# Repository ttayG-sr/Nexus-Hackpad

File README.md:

# Nexus-Hackpad
  Nexus Pad is a 9-key macro pad with a rotary encoder and an OLED, with the switches illuminated by LED backlighting! It is made for compact keyboard gaming, specifically Valorant, and, in the future, a Home Control Panel for smart devices; it functions using QMK firmware.

## Features:
- 9 MX-Style switches
  
- Rotary Encoder
  
- 0.91 inch, 128x32 OLED Screen
  
- 9 SK6812 Mini-E LEDs
  
- 70mm x 100mm Custom PCB
  
- 2 Part Custom Case
  
- All brought together with the Seeed XIAO RP2040 using QMK firmware
  
## CAD Model:
  It is made with a sandwich-style mount, using supports to elevate the PCB so the USB port can fit, and the switches and everything else have the necessary tolerance. 

  The PCB is sandwiched between the bottom case, which has the supports, and the top plate, all fastened with M3 Heat Inserts and screws.
Additionally, I rounded everything for moderate viewing angles for the OLED and a more aesthetic look.

<p align="center">Exploded View:</p>

## PCB:
This is the PCB that connects all of my components and houses the brain of the Nexus Pad; it was all made in KiCAD.

<p align="center">Schematic:</p>

<p align="center">PCB:</p>

## Firmware Overview:

The Nexus Pad uses QMK (https://qmk.fm/) to operate.

- Key Bindings
  - 4 for abilities in Valorant
  - A Left Shift to walk in Valorant
  - Another layer in the future will be added for productivity tools
  - Will include support for VIA in the future for more customizability!
- The rotary encoder can control the volume; the press function doesn't work.
- I plan for the OLED to show CPU and GPU temperatures in the future using plugins, but for now it just displays "Nexus Pad"
- The LEDs have three lighting effects: breathing, rainbow mood, and snake.

## BOM:
- 1x SEEED Xiao RP2040
- 9x 1N4148 DO-35 Diodes
- 9x MX-Style switches
- 9x DSA Keycaps
- 9x SK6812 MINI-E LEDs
- 1x EC11 Rotary Encoder
- 1x 0.91" 128x32 OLED Display
- 1x PCB
- 4x M3x16mm screws
- 4x M3x5mx4mm heatset inserts
- 1x Bottom case (3D Printed)
- 1x Top plate (3D Printed)

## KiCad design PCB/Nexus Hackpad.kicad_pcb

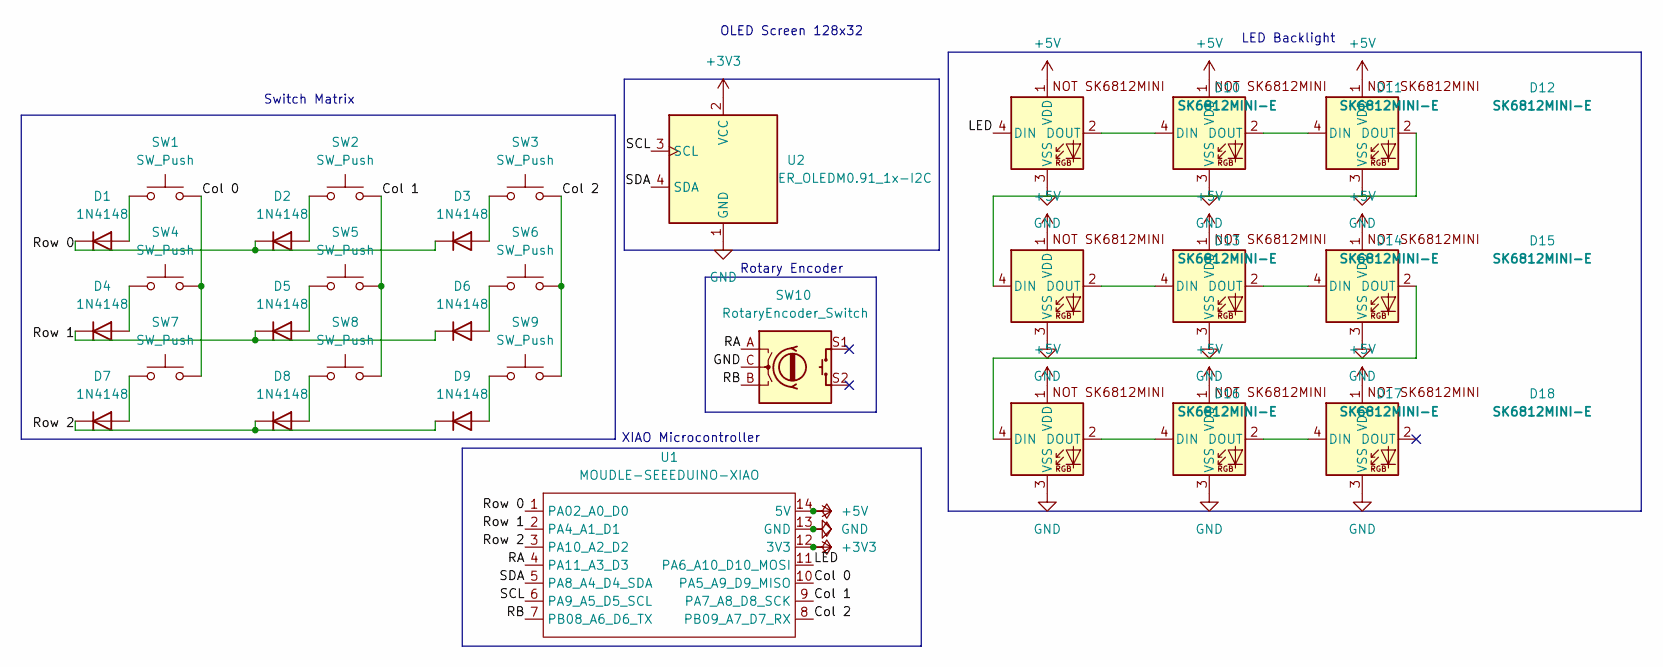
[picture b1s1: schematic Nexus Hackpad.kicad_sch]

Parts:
D1, D2, D3, D4, D5, D6, D7, D8, D9: 1N4148; D_DO-35_SOD27_P7.62mm_Horizontal
D10, D11, D12, D13, D14, D15, D16, D17, D18: SK6812MINI-E; SK6812MINI-E_fixed
SW1, SW2, SW3, SW4, SW5, SW6, SW7, SW8, SW9: SW_Push; SW_Cherry_MX_1.00u_PCB
SW10: RotaryEncoder_Switch; RotaryEncoder_Alps_EC11E-Switch_Vertical_H20mm
U1: MOUDLE-SEEEDUINO-XIAO; XIAO-Generic-Hybrid-14P-2.54-21X17.8MM
U2: ER_OLEDM0.91_1x-I2C

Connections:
+3V3: U1.12 (3V3), U2.2 (VCC)
+5V: D10.1 (VDD), D11.1 (VDD), D12.1 (VDD), D13.1 (VDD), D14.1 (VDD), D15.1 (VDD), D16.1 (VDD), D17.1 (VDD), D18.1 (VDD), U1.14 (5V)
/Col 0: SW1.2, SW4.2, SW7.2, U1.10 (PA5_A9_D9_MISO)
/Col 1: SW2.2, SW5.2, SW8.2, U1.9 (PA7_A8_D8_SCK)
/Col 2: SW3.2, SW6.2, SW9.2, U1.8 (PB09_A7_D7_RX)
/LED: D10.4 (DIN), U1.11 (PA6_A10_D10_MOSI)
/RA: SW10.A, U1.4 (PA11_A3_D3)
/RB: SW10.B, U1.7 (PB08_A6_D6_TX)
/Row 0: D1.1 (K), D2.1 (K), D3.1 (K), U1.1 (PA02_A0_D0)
/Row 1: D4.1 (K), D5.1 (K), D6.1 (K), U1.2 (PA4_A1_D1)
/Row 2: D7.1 (K), D8.1 (K), D9.1 (K), U1.3 (PA10_A2_D2)
/SCL: U1.6 (PA9_A5_D5_SCL), U2.3 (SCL)
/SDA: U1.5 (PA8_A4_D4_SDA), U2.4 (SDA)
GND: D10.3 (VSS), D11.3 (VSS), D12.3 (VSS), D13.3 (VSS), D14.3 (VSS), D15.3 (VSS), D16.3 (VSS), D17.3 (VSS), D18.3 (VSS), SW10.C, U1.13 (GND), U2.1 (GND)
unnamed: D1.2 (A), SW1.1
unnamed: D2.2 (A), SW2.1
unnamed: D3.2 (A), SW3.1
unnamed: D4.2 (A), SW4.1
unnamed: D5.2 (A), SW5.1
unnamed: D6.2 (A), SW6.1
unnamed: D7.2 (A), SW7.1
unnamed: D8.2 (A), SW8.1
unnamed: D9.2 (A), SW9.1
unnamed: D10.2 (DOUT), D11.4 (DIN)
unnamed: D11.2 (DOUT), D12.4 (DIN)
unnamed: D12.2 (DOUT), D13.4 (DIN)
unnamed: D13.2 (DOUT), D14.4 (DIN)
unnamed: D14.2 (DOUT), D15.4 (DIN)
unnamed: D15.2 (DOUT), D16.4 (DIN)
unnamed: D16.2 (DOUT), D17.4 (DIN)
unnamed: D17.2 (DOUT), D18.4 (DIN)

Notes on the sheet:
Rotary Encoder
XIAO Microcontroller
LED Backlight
OLED Screen 128x32
Switch Matrix

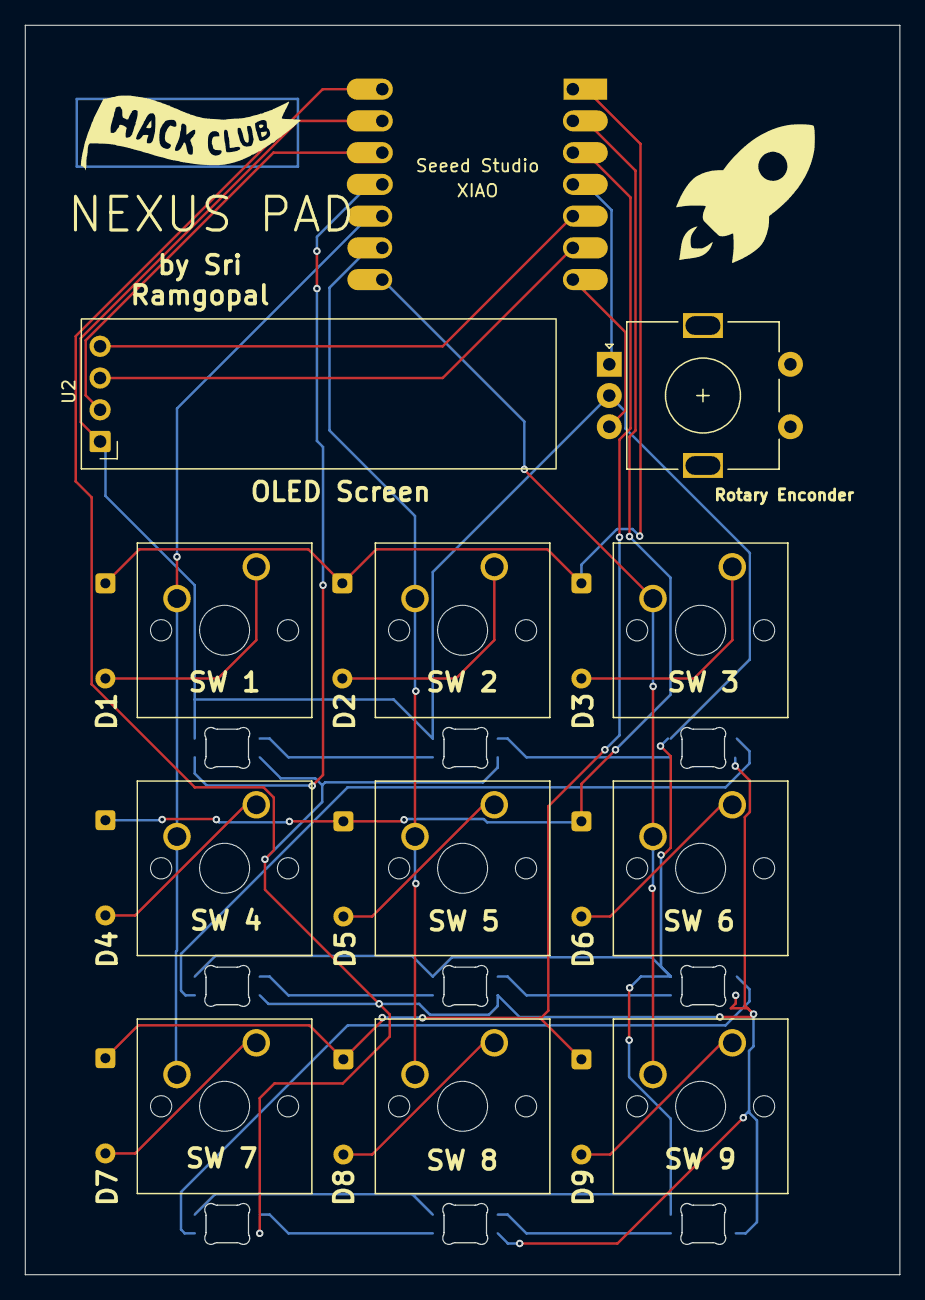
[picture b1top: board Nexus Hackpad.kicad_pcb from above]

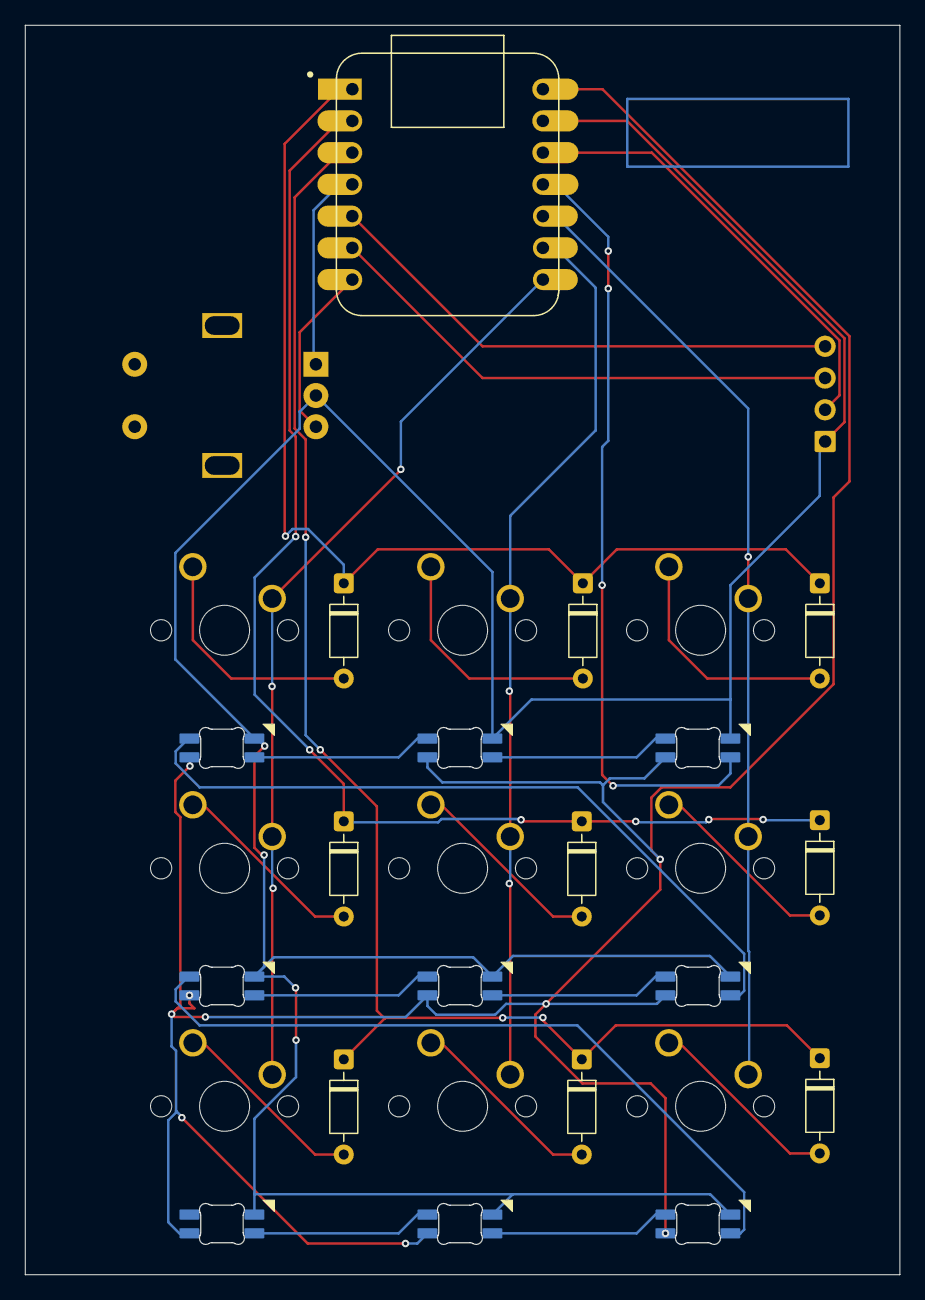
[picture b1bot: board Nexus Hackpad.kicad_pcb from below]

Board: 2 copper layers, 70.0 x 100.0 mm, 30 parts (10 on the bottom side), 31 nets.
